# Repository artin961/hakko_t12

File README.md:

Soldering IRON controller fot hakko t12 tips based on atmega328p-pu muicrocontroller (Arduino UNO/NANO)

## Story
In this project i will show you how to create your own soldering iron controller for amazing Hakko T12 tips on Arduino. This is my first soldering controller for hakko T12 tips.

The major update was performed 04/14/2020:

Support for optional TILT/REED switch added.
Support for optional ambient temperature sensor added.
Calibration procedure algorithm updated.
New menu items added.
Up to 42 tips can be activated from the whole-tips list using activation menu. You can select the tips you are going to use with this controller.
You have to update your hardware according to the updated schematics if you want use ambient temperature sensor or TILT/REED switch. Or you can continue to use your existing hardware. Please, see the detailed description below.

## The controller is working
The Hakko T12 soldering tips are amazing tools for soldering: they heat very fast and can reach very high temperatures in a short period of time. Each tip have a built-in thermo couple to control its temperature very accurately. Also, using appropriate handle, you can replace the tip on the fly in 1 second.

The main features of this controller are:

PID algorithm used to manage the supplied power. This allows you to keep the required temperature of the tip very accurate.
The controller supports individual calibration of the tip by three reference points: 200, 300 and 400 degrees Celsius.
There is a calibration procedure in the controller simplifying the tip calibration process. The calibration procedure has been updated 14/04/2020.
The controller uses high-frequency PWM signal to control the supplied power and controller is working silently.
Accelerated rotary encoder algorithm implemented in the controller. While the encoder rotated slowly, the temperature preset changes by 1 degree and if you turn the knob fast, the temperature preset would be increased by 5 degrees.
The temperature can be displayed in two degrees: Celsius or Fahrenheit.
The controller supports TILT switch in the handle or REED switch in the soldering station base to activate low power (standby) mode.
The Hakko T12 soldering tips

The first thing you need to use these tips is a handle. There are a several handles for these tips in the market and I would like to recommend you to order the FX-9501 one. This handle has a light weight, very convenient and has a good quality socket (inside) to plug the tip. You can easily change the tip on the fly if you wish.

The tip has 3 wires: "+", "-" and earth ground. The heater is connected consequently with the thermo couple inside the tip, so it required two wires to be connected to the controller only.

First problem: the connector
First problem was the original connector of the handle. It is so rarely used, I could not find the socket for it, so I used the aviation plug GX12-5.

## Connect the sensor
As I mentioned before, the tip uses two wires to heat and to check the temperature. The controller puts some power to the IRON for some period then turns the power off and checks the tip temperature. The thermo couple generates very small voltage, about several millivolts, so to check this voltage operating amplifier is implemented in the schematics. But the amplifier does not like a 24 volts on its input and could be destroyed. Hopefully, this problem has been already solved by qualified people: they used Zener diode to limit the voltage on the input circuit. You can see the sensor part of the schematics on the picture below.

The main component of the schematics is a dual channel operating amplifier, ad822. It has a mosfet transistors on its input, is rail-to-rail and has very low noise. I have bought couple of amplifiers on eBay supplier for $5 each. Now you can find much more cheaper fake variant of this amplifier on Chinese suppliers. Unfortunately, this variant is much noisy. So it is better to use another non-expensive amplifier, mcp602 for this controller. Also, you can use ad823 op-amp as well.

The temperature of the iron is checked by the first amplifier on pins 1, 2, 3 and the current through the iron is checked by the second amplifier on pins 5, 6, 7. Checking the current through the IRON allows to ensure that the tip is connected to the controller. When the tip removed from the handle the controller starts 'change tip' procedure allowing you to select new tip from the tip list menu.

## Supplying power to the iron
The first idea of supplying power to the iron was to use PWM signal by analogWrite() function of Arduino. Unfortunately, the default frequency of the Arduino PWM signal is 490 Hz and the iron makes a noise while heating. It was ridiculous. To make the iron silent the high-frequency PWM signal implemented on TIMER1 running 31250 Hz to power the IRON. To allow the FET managing such high frequency PWM signal, the three transistor mosfet driver is implemented in the schematics.

For short, the FET has near zero resistance while it is open and about infinite resistance when it is closed. But in the intermediate state (while the FET is switching) the resistance become valuable and the FET starts heating. Because the FET has capacitance in the gate that requires time to charge or discharge. This forum thread explains the problem in details.

Zener diode (18V) is used to limit the Gate voltage (Vgs) of the FET while it is open because the power supply voltage is higher than maximum value of mosfet vgs voltage. The fast recoverable diode FR104 removes the power from the iron when the FET is closed.

You can replace this diode with another one, but you must use fast recoverable diode.

The inductance shown in the schematics is a tor of outer diameter about 1.5 cm wired with 20 cm long copper. The inductance is about 50-100 uH. This inductance prevents flickering of the electricity while the iron is heating.

Support for TILT/REED switch and ambient temperature sensor
Support for hardware Tilt or Reed switch was added in the firmware 14/04/2020. This feature allows to turn the IRON into standby mode in case of IRON inactivity or when IRON has been put into base.

The tilt switch can be put into soldering iron handle. When the iron was laying still for specified period of time, the standby mode would be activated.

The reed switch can be placed into the iron base, and should be shorten when the iron put on the base. In this case, you can setup lower value for standby mode timeout.

Low temperature and timeout can be setup through menu.

Ambient temperature sensor NTC-type of 10kOhm is supported by the firmware. You can install it into the iron handle also.

## Build the controller
The complete controller schematics is shown on the picture below. The controller is built on the atmega328p-pu micro controller running at 16 MHz. You can use Arduino nano or UNO board if you wish. They are completely compatible.

There are some sockets that should be explained in the schematics. SV1 is a serial connector allowing load the sketch to the Arduino. You can use USB to UART converter to program the controller. JP1 is a lcd0802 connector. JP2 & JP3 are actually a single 5-pin aviation plug used to connect soldering iron handle. SV2 connector is used to attach rotary encoder.

As you can see on the picture, the DC-DC converter is used to get 5v for the operating amplifier and to power the micro controller. The WSTECH DC-DC isolated converter is implemented. It supplies very stable power for the operating amplifier.

This DC-DC converter could be replaced with another one DC-DC converter by ND like the one shown on the picture below

In case you failed to find any of isolated DC-DC converter, it is possible to replace it with non-isolated DC-DC 24v->5v converter + isolated DC-DC converter b0505s 5v->5v. See pictures below.

The software sketch can be downloaded from the GitHub repository.

Tune the controller
Note: The external thermo couple required to tune the potentiometer. To perform tuning procedure more precisely, apply a solder drop to the contact between the thermocouple and the soldering tip rod.

In the controller schematics you can see the potentiometer R10 (500kOhm) that tunes the operation amplifier to get the expected temperature readings at Arduino pin A0. You can use different operating amplifier, you can use different tips so this potentiometer increases the controller flexibility. This potentiometer should be tuned at least once when you created the controller. The main idea is that the controller reads the voltage from the thermo couple through the ADC and gets some integer data in the interval 0-1023 depending of the voltage on pin A0. The near the voltage to 5v the near the readings to the 1023. The potentiometer should be tuned so when the iron temperature become 400 centares, the ADC reading should be about 900.

To tune the potentiometer, select 'tune' menu item from the setup menu. The iron starts heating. The controller displays the temperature readings from A0 pin in the internal units (0-1023) in this mode. By rotating the encoder you can adjust the supplied power to the iron. Try to keep the iron temperature as near to 400 degrees of centigrade as possible (use external thermometer). At the beginning you can increase the supplied power to the maximum value to speed up the iron heating, then decrease the power to keep the temperature at the 400 degrees. When you stabilize the iron temperature near 400 degrees, rotate the multi-turn potentiometer handle to get the sensor readings near 900. Ensure that this readings is not the maximum one, rotate the variable potentiometer and get 930-950, then return back to 900. It is important because the controller should be able to measure the temperature greater than 400 degrees of Centigrade.

When the variable potentiometer is adjusted, press and hold the encoder handle for about 2 seconds. The initial setup procedure now is complete.

Note: the sketch assumes that the working temperature interval of the soldering iron is 180 - 400 degrees of Celsius. It is possible to change this interval by editing constants in the program sketch before you plan to tune the controller.

It is recommended to use the thick tip that produces the highest voltage to perform the tune procedure. For example, T12-K, T12-D52 or so.

The controller modes
The controller has several modes:

## Standby mode
Main working mode (keep the preset temperature)
Power mode (keep the supplied power)
Setup mode
Calibration mode
Tune mode (the initial potentiometer setup procedure)
When the controller is just powered on, the standby mode is activated. In this mode the soldering iron is powered off. The main display shows the following information:

The preset temperature on the left side of the upper line (in units selected - Celsius or Fahrenheit);
The 'OFF' message on the right side of the upper line indicating that the iron is powered off;
The current temperature of the iron is on the left side of the second line;
In case the iron tip is not connected to the controller, the controller starts tip selection mode. Select the tip name you are going to insert from the tip list, then insert the tip.

Note: In the update firmware version, up to 42 soldering iron tips can be activated and used, but the whole tip list supported. First, you have to select (activate) the tips you are going to use. To do so, select "activ." menu item.

The preset temperature can be adjusted by rotating the encoder handle while the iron is powered off. To power on the soldering iron, push the encoder handle lightly. The main working mode of controller will be activated. Now the controller keeps the iron temperature near the preset one.

In the main mode the display shows the following information:

The preset temperature on the left side of the upper line (in units selected - Celsius or Fahrenheit)
The 'ON' message on the right side of the upper line indicating that the iron is powered on and is still heating. When the iron reaches the preset temperature, the 'rdy ' (ready) message will be displayed; When the controller activates the standby mode, the 'stb' (standby) message will be displayed.
The current temperature of the iron is displayed in the left side of the second line;
The power supplied to the iron (in percents of the maximum allowable power) is displayed in the right side of the screen;
By rotating the encoder it is possible to change the preset temperature. The message 'ON' would be showed again till the iron would reached the new preset temperature. To return to the standby mode, press the encoder handle lightly.

In the main mode, the controller checks that the iron is working properly.

The power mode can be switched on by long pressing the encoder while it is in the main mode. In the power mode, you can adjust the power supplied to the soldering iron manually by rotating encoder. In the power mode the screen shows the power supplied to the iron in the internal units and the iron temperature in human readable units. By pressing the encoder toggles on-off power in the power mode. Long press of the rotary encoder handle will return the controller from power mode to the main working mode.

## The controller menu
To get to the controller setup menu, long press the encoder in standby or tip selection mode. In the setup mode the configuration parameters can be adjusted. There are 11 menu entries in this mode:

temperature units (Celsius or Fahrenheit)
buzzer (ON/OFF)
Switch type: tilt/reed
Ambient temperature sensor (enabled/disabled)
Standby temperature (if zero, disables automatic low-power mode)
Standby timeout (seconds)
automatic power-off timeout (minutes)
the iron calibration ('calib.')
the iron tips activation ('activ.')
initial setup procedure ('tune')
save the changes
cancel the changes
Rotate the handle to select the menu item. To change the selected item, press lightly on the encoder handle. After adjusting the parameter, press the handle again to return to the setup menu. Long press of the encoder handle can be used to return back to standby mode and save the parameters in the EEPROM.

## Activate soldering tips
The controller supports near all tips available in the world, if not, you can add new tip at any time by editing iron_tips.cpp source file. It is not convenient to select next tip from the whole list, so you have to activate the tips you are going to use from the whole-tip list. To do so, select 'activ.' menu item from the setup menu, rotate encoder to select required tip and press the encoder to toggle tip activation. The controller saves the tip calibration data of all active tips in the EEPROM. Up to 42 active tips are supported by this firmware version.

To finish activation procedure, long press the encoder.

Note: The setup menu is available from standby mode or from 'tip selection' mode by long press the encoder.

## Calibrate the soldering tip
Note:The external thermocouple required to calibrate the iron tip. To perform calibration procedure more precisely, apply a solder drop to the contact between the thermocouple and the soldering tip rod. To heat-up the tip and apply soldering rod, you can use tune procedure (see above).

The controller reads the temperature in internal units (0-1023) by reading the voltage on A0 Arduino pin. It is convenient for us to use the human readable units like degrees of Celsius or Fahrenheit. There are three reference points for soldering iron calibration: 200, 300 and 400 degrees of Celsius. The controller saves internal readings for these three reference points and uses them to convert the temperature from internal reading to human readable values.

The calibration process requires to check the temperature in 7-8 points. Select 'calib.' menu item from the setup menu to start calibration process. The calibration screen would be displayed with 'OFF" message indicating the iron tip is ready to be calibrated. Switch-on the iron by pressing the encoder handle. The soldering iron starts heating.

The PID algorithm allows reach the desired temperature in short time. When the reference point temperature would be reached, the controller would 'beep' indicating it is ready to check the temperature by external sensor. Wait a little allowing the temperature to stabilize, then check the real temperature of the soldering iron by external sensor. Then rotate the handle of the rotary encoder and enter the real temperature of the iron. Press the encoder handle lightly. The controller saves the real temperature of the reference point and continues to check the temperature at next reference point. The reference point number would be displayed on the first display string. As soon as all measurements would be finished, the calibration procedure finished and the controller would return at main mode.

## Automatic power-off feature
The automatic switch-off feature required of using tilt or reed switch in the updated firmware version,

Updated 04/24/2020.
 - Fixed issue of accidentally switching from Celsius to Fahrenheit
 - No more checking for iron connectivity while it is active
 
Updated 04/18/2020. The ambient temperature support restored.
 - Fixed wrong temperature readings issue in keepTemp() procedure.
 - Fixed standby mode actiovation issue.

Updated 04/16/2020. To increase stability, removed suport for ambient temperature sensor.

Updated 04/14/2020. Major changes include schematics update.
- Support for optional TILT/REED switch added.
- Support for optional ambient temperature sensor added.
- Calibration procedure algotithm updated.
- New menu items added.

Because the major changes were made, the prevoius stable firmware version has been moved in OLD folder for backup.

Updated 09/05/2019. Preset temperature jumps when finished rotating the encoder issue fixed

Updated 04/18/2019. Two display configuration support added. You should select appropriate display in the config.h file

Updated 01/14/2018. Fixed bug with the IRON overheat. New procedure in the tip configutration implemented. 

Updated 11/23/2017. Fixed bug with cold temperature detection. New criteria for ready state implemented in the working mode and in the tip configuration mode.

Updated 10/21/2017. New PID parameters used. 

Updated 10/14/2017. Fixed unstable work with 'thin' soldering tips such as T12-BC1, T12-JL02, T12-IL, T12-D12 by Increasing the frequency of temperature sampling to 50 Hz. New PID coefficients implemented.

Updated 7/1/2017. New software features are available: new per-tip calibration and high-frequency temperature check by Timer1, now no addititional software library required.

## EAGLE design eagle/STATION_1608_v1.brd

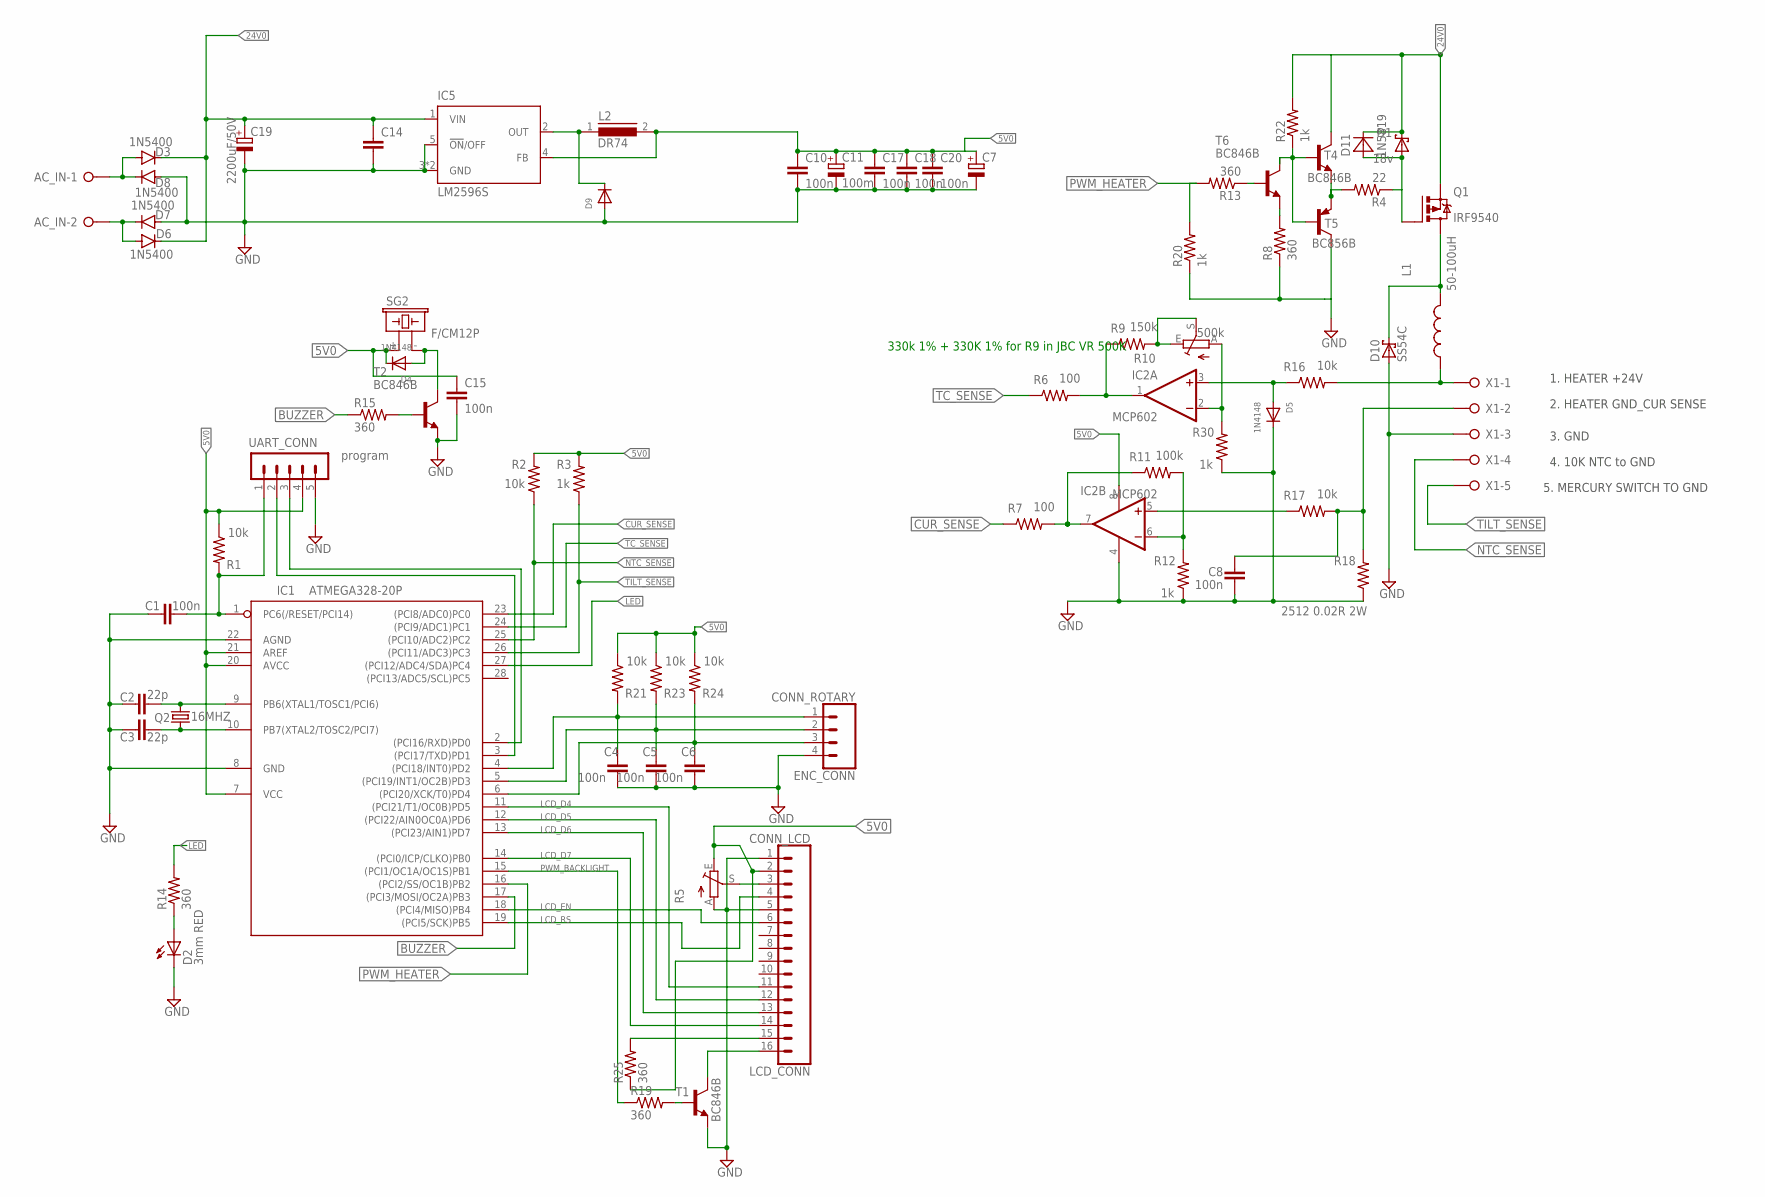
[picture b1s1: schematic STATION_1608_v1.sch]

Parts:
AC_IN: W237-02P; W237-132
C1, C4, C5, C6, C8, C10, C14, C17, C18, C20: 100n; C0805
C2, C3: 22p; C0805
C7: CPOL-EUE3.5-8; E3,5-8
C11: 100m; E3,5-8
C15: 100n; C0805K
C19: 2200uF/50V; E7,5-16
D1: 18v; SOD80C
D2: 3mm RED; LED5MM
D3, D6, D7, D8: 1N5400; DO201-15
D4, D5: 1N4148; SOD-123
D9: DIODESMA; SMADIODE
D10: SS54C; SMC
D11: 1N5819; SMA
ENC_CONN: CONN_ROTARY; 1X04_LONGPADS
IC1: ATMEGA328-20P; DIL28-3
IC2: MCP602; DIL08
IC5: LM2596S; TO263-5
L1: 50-100uH; IRF46
L2: DR74
LCD_CONN: CONN_LCD; 1X16_LONGPADS
Q1: IRF9540; TO220BV
Q2: 16MHZ; HC49/S
R1, R2, R16, R17, R21, R23, R24: 10k; M0805
R3, R12, R20, R22, R30: 1k; M0805
R4: 22; M0805
R5: TRIM_EU-RJ9W; RJ9W
R6, R7: 100; M0805
R8, R13, R14, R15, R19, R25: 360; M0805
R9: 150k; M0805
R10: 500k; RJ9W
R11: 100k; M0805
R18: 2512 0.02R 2W; R2512
SG2: F/CM12P
T1, T2, T4, T6: BC846B; SOT23-BEC
T5: BC856B; SOT23-BEC
UART_CONN: program; MA05-1
X1: W237-05P; W237-5P

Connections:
5V0: C7.+, C10.1, C11.+, C15.1, C17.1, C18.1, C20.1, D4.C, IC1.7 (VCC), IC1.20 (AVCC), IC1.21 (AREF), IC2.8 (V+), IC5.4 (FB), L2.2, LCD_CONN.2, R1.1, R2.2, R3.2, R5.E, R21.1, R23.1, R24.1, R25.1, SG2.+ (1), UART_CONN.4
24V0: C14.1, C19.+, D1.1 (K), D3.C, D6.C, D11.C, IC5.1 (VIN), Q1.S, R22.2, T4.C
BUZZER: IC1.17 ((PCI3/MOSI/OC2A)PB3), R15.1
CUR_SENSE: IC1.23 ((PCI8/ADC0)PC0), R7.1
GND: C1.1, C2.1, C3.1, C4.2, C5.2, C6.2, C7.-, C8.2, C10.2, C11.-, C14.2, C15.2, C17.2, C18.2, C19.-, C20.2, D2.K (C), D5.C, D7.A, D8.A, D9.A, D10.A, ENC_CONN.4, IC1.8 (GND), IC1.22 (AGND), IC2.4 (V-), IC5.3 (GND), IC5.5 (!ON!/OFF), IC5.6 (GND), LCD_CONN.1, LCD_CONN.5, R5.A, R8.1, R12.1, R18.1, R20.1, R30.1, T1.E, T2.E, T5.C, UART_CONN.5, X1.3
LCD_D4: IC1.11 ((PCI21/T1/OC0B)PD5), LCD_CONN.11
LCD_D5: IC1.12 ((PCI22/AIN0OC0A)PD6), LCD_CONN.12
LCD_D6: IC1.13 ((PCI23/AIN1)PD7), LCD_CONN.13
LCD_D7: IC1.14 ((PCI0/ICP/CLKO)PB0), LCD_CONN.14
LCD_EN: IC1.18 ((PCI4/MISO)PB4), LCD_CONN.6
LCD_RS: IC1.19 ((PCI5/SCK)PB5), LCD_CONN.4
LED: IC1.27 ((PCI12/ADC4/SDA)PC4), R14.2
MOSFET_GATE: D1.2 (A), D11.A, Q1.G, R4.1
unnamed: C2.2, IC1.9 (PB6(XTAL1/TOSC1/PCI6)), Q2.2
unnamed: C3.2, IC1.10 (PB7(XTAL2/TOSC2/PCI7)), Q2.1
unnamed: C4.1, ENC_CONN.1, IC1.4 ((PCI18/INT0)PD2), R21.2
unnamed: R4.2, T4.E, T5.E
unnamed: C5.1, ENC_CONN.2, IC1.5 ((PCI19/INT1/OC2B)PD3), R23.2
unnamed: D9.C, IC5.2 (OUT), L2.1
unnamed: IC1.3 ((PCI17/TXD)PD1), UART_CONN.2
unnamed: IC1.2 ((PCI16/RXD)PD0), UART_CONN.3
unnamed: C6.1, ENC_CONN.3, IC1.6 ((PCI20/XCK/T0)PD4), R24.2
unnamed: AC_IN.2, D6.A, D7.C
unnamed: AC_IN.1, D3.A, D8.C
unnamed: LCD_CONN.3, R5.S
unnamed: LCD_CONN.16, T1.C
unnamed: LCD_CONN.15, R25.2
unnamed: R15.2, T2.B
unnamed: IC2.7 (OUT), R7.2, R11.1
unnamed: R13.1, T6.B
unnamed: IC2.6 (-IN), R11.2, R12.2
unnamed: R22.1, T4.B, T5.B, T6.C
unnamed: IC2.5 (+IN), R17.1
unnamed: R9.2, R10.E, R10.S
unnamed: IC2.2 (-IN), R10.A, R30.2
unnamed: IC2.1 (OUT), R6.2, R9.1
unnamed: D5.A, IC2.3 (+IN), R16.1
unnamed: R8.2, T6.E
unnamed: C1.2, IC1.1 (PC6(/RESET/PCI14)), R1.2, UART_CONN.1
unnamed: L1.1, R16.2, X1.1
unnamed: D10.C, L1.2, Q1.D
unnamed: D4.A, SG2.- (2), T2.C
unnamed: R19.2, T1.B
unnamed: D2.A, R14.1
unnamed: C8.1, R17.2, R18.2, X1.2
NTC_SENSE: IC1.25 ((PCI10/ADC2)PC2), R2.1, X1.4
PWM_BACKLIGHT: IC1.15 ((PCI1/OC1A/OC1S)PB1), R19.1
PWM_HEATER: IC1.16 ((PCI2/SS/OC1B)PB2), R13.2, R20.2
TC_SENSE: IC1.24 ((PCI9/ADC1)PC1), R6.1
TILT_SENSE: IC1.26 ((PCI11/ADC3)PC3), R3.1, X1.5

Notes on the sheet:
2. HEATER GND_CUR SENSE
3. GND
4. 10K NTC to GND
5. MERCURY SWITCH TO GND
1. HEATER +24V
330k 1% + 330K 1% for R9 in JBC VR 500K

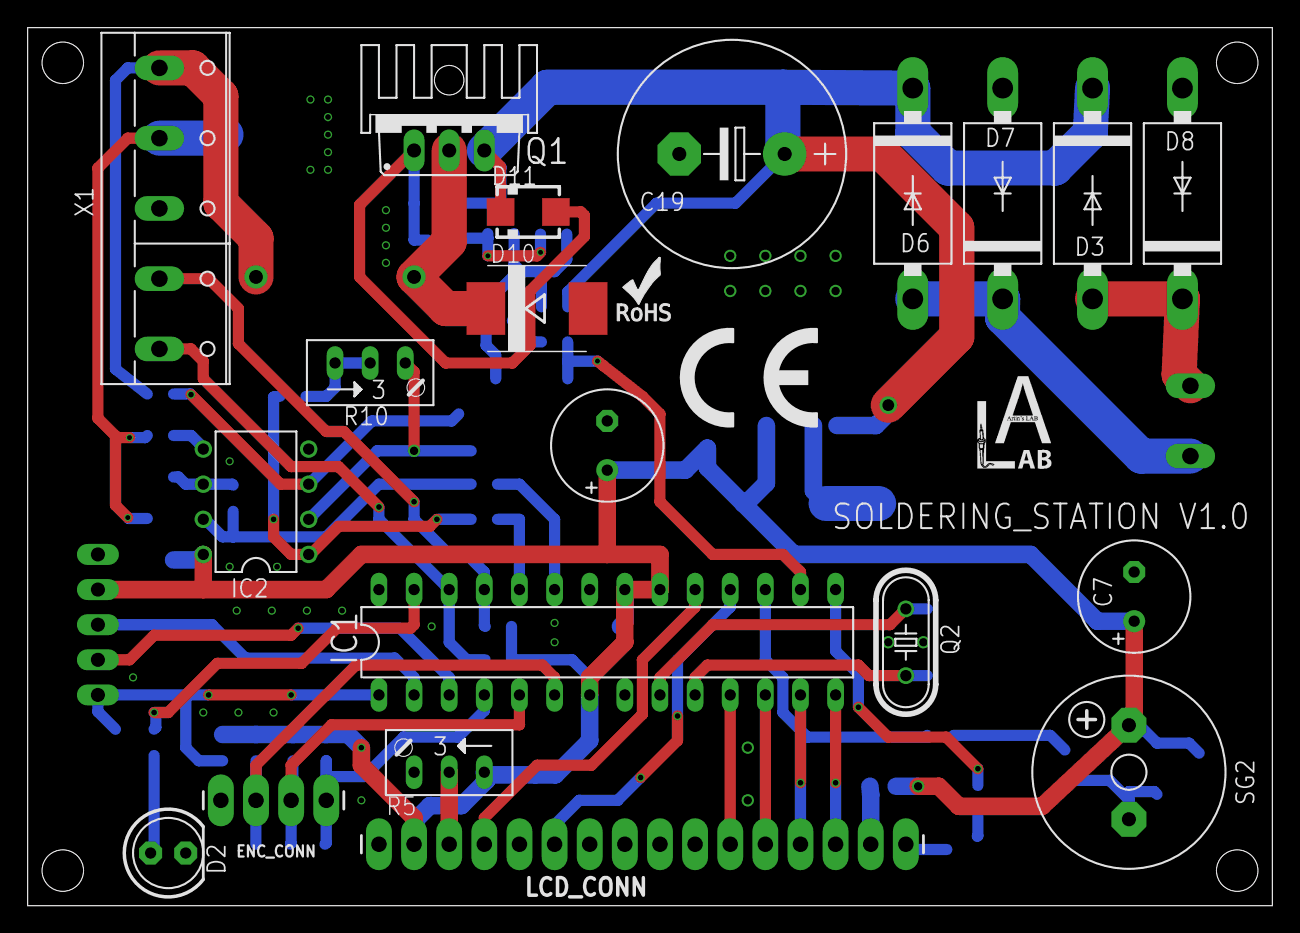
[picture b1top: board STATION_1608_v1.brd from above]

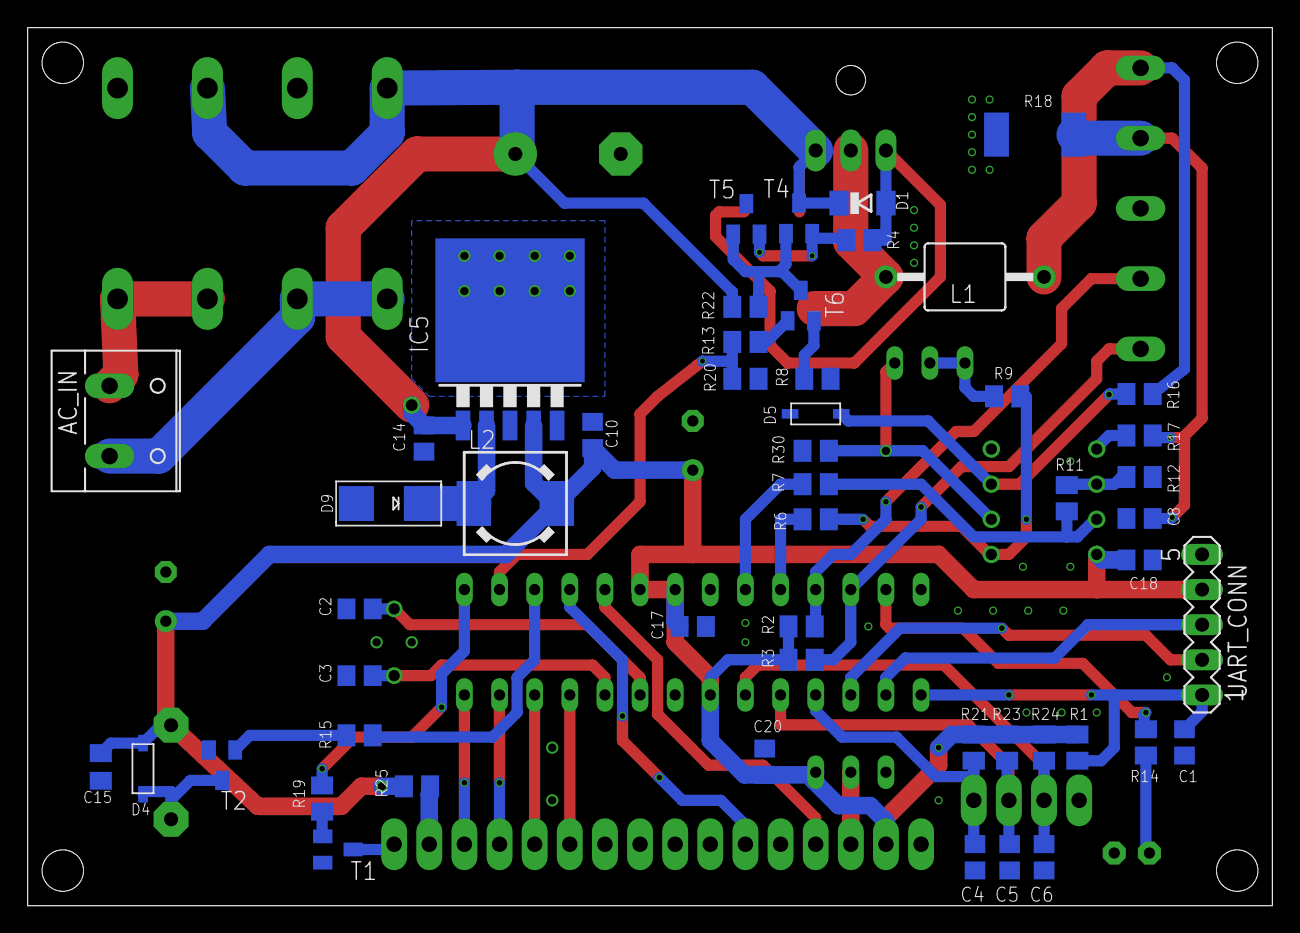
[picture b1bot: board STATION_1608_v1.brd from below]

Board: 2 copper layers, 90.0 x 63.5 mm, 75 parts (51 on the bottom side), 50 nets.

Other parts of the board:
U$1: SK-95
U$2: ALAB_LOGO
U$3: ROHS_LOGO_0.18_IN
U$4: CE_7.3MM

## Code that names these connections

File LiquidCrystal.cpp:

#include "LiquidCrystal.h"

#include <stdio.h>
#include <string.h>
#include <inttypes.h>
#include "Arduino.h"
#include "Config.h"

// When the display powers up, it is configured as follows:
//
// 1. Display clear
// 2. Function set:
//    DL = 1; 8-bit interface data
//    N = 0; 1-line display
//    F = 0; 5x8 dot character font
// 3. Display on/off control:
//    D = 0; Display off
//    C = 0; Cursor off
//    B = 0; Blinking off
// 4. Entry mode set:
//    I/D = 1; Increment by 1
//    S = 0; No shift
//
// Note, however, that resetting the Arduino doesn't reset the LCD, so we
// can't assume that its in that state when a sketch starts (and the
// LiquidCrystal constructor is called).

LiquidCrystal::LiquidCrystal()
{
  _displayfunction = LCD_4BITMODE | LCD_1LINE | LCD_5x8DOTS;
}

void LiquidCrystal::begin(uint8_t cols, uint8_t lines, uint8_t dotsize) {
  //Init IO
  BACKLIGHT_PORT &= ~BACKLIGHT_BITMASK;
  BACKLIGHT_DDR |= BACKLIGHT_BITMASK;

  if (lines > 1) {
    _displayfunction |= LCD_2LINE;
  }
  _numlines = lines;

  setRowOffsets(0x00, 0x40);

  // for some 1 line displays you can select a 10 pixel high font
  if ((dotsize != LCD_5x8DOTS) && (lines == 1)) {
    _displayfunction |= LCD_5x10DOTS;
  }

  // Clear ports and make them outputs
  RS_EN_PORT &= ~(RS_BITMASK | EN_BITMASK);
  RS_EN_DDR |= (RS_BITMASK | EN_BITMASK);

  D012_PORT &= ~D012_BITMASK;
  D012_DDR |= D012_BITMASK;

  D3_PORT &= ~D3_BITMASK;
  D3_DDR |= D3_BITMASK;


  // SEE PAGE 45/46 FOR INITIALIZATION SPECIFICATION!
  // according to datasheet, we need at least 40ms after power rises above 2.7V
  // before sending commands. Arduino can turn on way before 4.5V so we'll wait 50
  delayMicroseconds(50000);
  // Now we pull both RS and R/W low to begin commands
  // we start in 8bit mode, try to set 4 bit mode
  write4bits(0x03);
  delayMicroseconds(4500); // wait min 4.1ms

  // second try
  write4bits(0x03);
  delayMicroseconds(4500); // wait min 4.1ms

  // third go!
  write4bits(0x03);
  delayMicroseconds(150);

  // finally, set to 4-bit interface
  write4bits(0x02);

  // finally, set # lines, font size, etc.
  command(LCD_FUNCTIONSET | _displayfunction);

  // turn the display on with no cursor or blinking default
  _displaycontrol = LCD_DISPLAYON | LCD_CURSOROFF | LCD_BLINKOFF;
  display();

  // clear it off
  clear();

  // Initialize to default text direction (for romance languages)
  _displaymode = LCD_ENTRYLEFT | LCD_ENTRYSHIFTDECREMENT;
  // set the entry mode
  command(LCD_ENTRYMODESET | _displaymode);
}

void LiquidCrystal::setRowOffsets(int row0, int row1)
{
  _row_offsets[0] = row0;
  _row_offsets[1] = row1;
}

/********** high level commands, for the user! */
void LiquidCrystal::backlight() {
  //BACKLIGHT_PORT |= BACKLIGHT_BITMASK;
  OCR1A=255;
}
void LiquidCrystal::noBacklight() {
  //BACKLIGHT_PORT &= ~BACKLIGHT_BITMASK;
  OCR1A=60;
}
void LiquidCrystal::clear()
{
  command(LCD_CLEARDISPLAY);  // clear display, set cursor position to zero
  delayMicroseconds(2000);  // this command takes a long time!
}

void LiquidCrystal::home()
{
  command(LCD_RETURNHOME);  // set cursor position to zero
  delayMicroseconds(2000);  // this command takes a long time!
}

void LiquidCrystal::setCursor(uint8_t col, uint8_t row)
{
  const size_t max_lines = sizeof(_row_offsets) / sizeof(*_row_offsets);
  if ( row >= max_lines ) {
    row = max_lines - 1;    // we count rows starting w/0
  }
  if ( row >= _numlines ) {
    row = _numlines - 1;    // we count rows starting w/0
  }

  command(LCD_SETDDRAMADDR | (col + _row_offsets[row]));
}

// Turn the display on/off (quickly)
void LiquidCrystal::noDisplay() {
  _displaycontrol &= ~LCD_DISPLAYON;
  command(LCD_DISPLAYCONTROL | _displaycontrol);
}
void LiquidCrystal::display() {
  _displaycontrol |= LCD_DISPLAYON;
  command(LCD_DISPLAYCONTROL | _displaycontrol);
}

// Turns the underline cursor on/off
void LiquidCrystal::noCursor() {
  _displaycontrol &= ~LCD_CURSORON;
  command(LCD_DISPLAYCONTROL | _displaycontrol);
}
void LiquidCrystal::cursor() {
  _displaycontrol |= LCD_CURSORON;
  command(LCD_DISPLAYCONTROL | _displaycontrol);
}

// Turn on and off the blinking cursor
void LiquidCrystal::noBlink() {
  _displaycontrol &= ~LCD_BLINKON;
  command(LCD_DISPLAYCONTROL | _displaycontrol);
}
void LiquidCrystal::blink() {
  _displaycontrol |= LCD_BLINKON;
  command(LCD_DISPLAYCONTROL | _displaycontrol);
}

// These commands scroll the display without changing the RAM
void LiquidCrystal::scrollDisplayLeft(void) {
  command(LCD_CURSORSHIFT | LCD_DISPLAYMOVE | LCD_MOVELEFT);
}
void LiquidCrystal::scrollDisplayRight(void) {
  command(LCD_CURSORSHIFT | LCD_DISPLAYMOVE | LCD_MOVERIGHT);
}

// This is for text that flows Left to Right
void LiquidCrystal::leftToRight(void) {
  _displaymode |= LCD_ENTRYLEFT;
  command(LCD_ENTRYMODESET | _displaymode);
}

// This is for text that flows Right to Left
void LiquidCrystal::rightToLeft(void) {
  _displaymode &= ~LCD_ENTRYLEFT;
  command(LCD_ENTRYMODESET | _displaymode);
}

// This will 'right justify' text from the cursor
void LiquidCrystal::autoscroll(void) {
  _displaymode |= LCD_ENTRYSHIFTINCREMENT;
  command(LCD_ENTRYMODESET | _displaymode);
}

// This will 'left justify' text from the cursor
void LiquidCrystal::noAutoscroll(void) {
  _displaymode &= ~LCD_ENTRYSHIFTINCREMENT;
  command(LCD_ENTRYMODESET | _displaymode);
}

// Allows us to fill the first 8 CGRAM locations
// with custom characters
void LiquidCrystal::createChar(uint8_t location, uint8_t charmap[]) {
  location &= 0x7; // we only have 8 locations 0-7
  command(LCD_SETCGRAMADDR | (location << 3));
  for (int i = 0; i < 8; i++) {
    write(charmap[i]);
  }
}

/*********** mid level commands, for sending data/cmds */

inline void LiquidCrystal::command(uint8_t value) {
  RS_EN_PORT &= ~RS_BITMASK;
  send(value);
}

inline size_t LiquidCrystal::write(uint8_t value) {
  RS_EN_PORT |= RS_BITMASK;
  send(value);
  return 1; // assume sucess
}

/************ low level data pushing commands **********/

// write either command or data, with automatic 4/8-bit selection
void LiquidCrystal::send(uint8_t value) {
  write4bits(value >> 4);
  write4bits(value);
}

void LiquidCrystal::write4bits(uint8_t value) {


  D012_PORT = (D012_PORT & ~D012_BITMASK) | ((value << 5) & D012_BITMASK); // Update PD5, PD6, PD7
  D3_PORT = (PORTB & ~D3_BITMASK) | ((value >> 3) & D3_BITMASK); // Update PB0


  RS_EN_PORT |= EN_BITMASK;
  delayMicroseconds(1);    // enable pulse must be >450ns
  RS_EN_PORT &= ~EN_BITMASK;
  delayMicroseconds(50);   // commands need > 37us to settle
}

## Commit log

2022-05-22 961 mod
2022-05-22 mods
2022-05-23 minor fixes
2023-08-24 refresh
2023-08-24 minor mods and bugfixes
2023-08-24 mminor chnges
2023-08-24 bugfixes
2024-03-17 revert back for tilt
2025-03-01 some changes
2025-03-18 add info from hackster.io
2025-03-20 config, empAVG verified working
2025-03-20 Encoder and PID ok
2025-03-20 Working encoder
2025-03-20 Compiles
2025-03-20 Working
2025-03-20 Display optimised and IO
2025-03-21 before tips optimisation
2025-03-21 tip optimisation
2025-03-21 UI optim encoder bugfix on write
2025-03-24 more optimisations
2025-03-28 working and tested
2025-03-28 Refactoring (#1)
    Optimized some finctions and files, Improved IO
2025-03-31 improve tilt sensing and thweak default settings

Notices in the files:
parts and their libraries:
SparkFun-Connectors: Licensing: Creative Commons ShareAlike 4.0 International - https://creativecommons.org/licenses/by-sa/4.0
globex: Copyright © 2012, Michel Stempin, All rights reserved
Licenced under Creative Commons CC BY-SA 3.0 license.
